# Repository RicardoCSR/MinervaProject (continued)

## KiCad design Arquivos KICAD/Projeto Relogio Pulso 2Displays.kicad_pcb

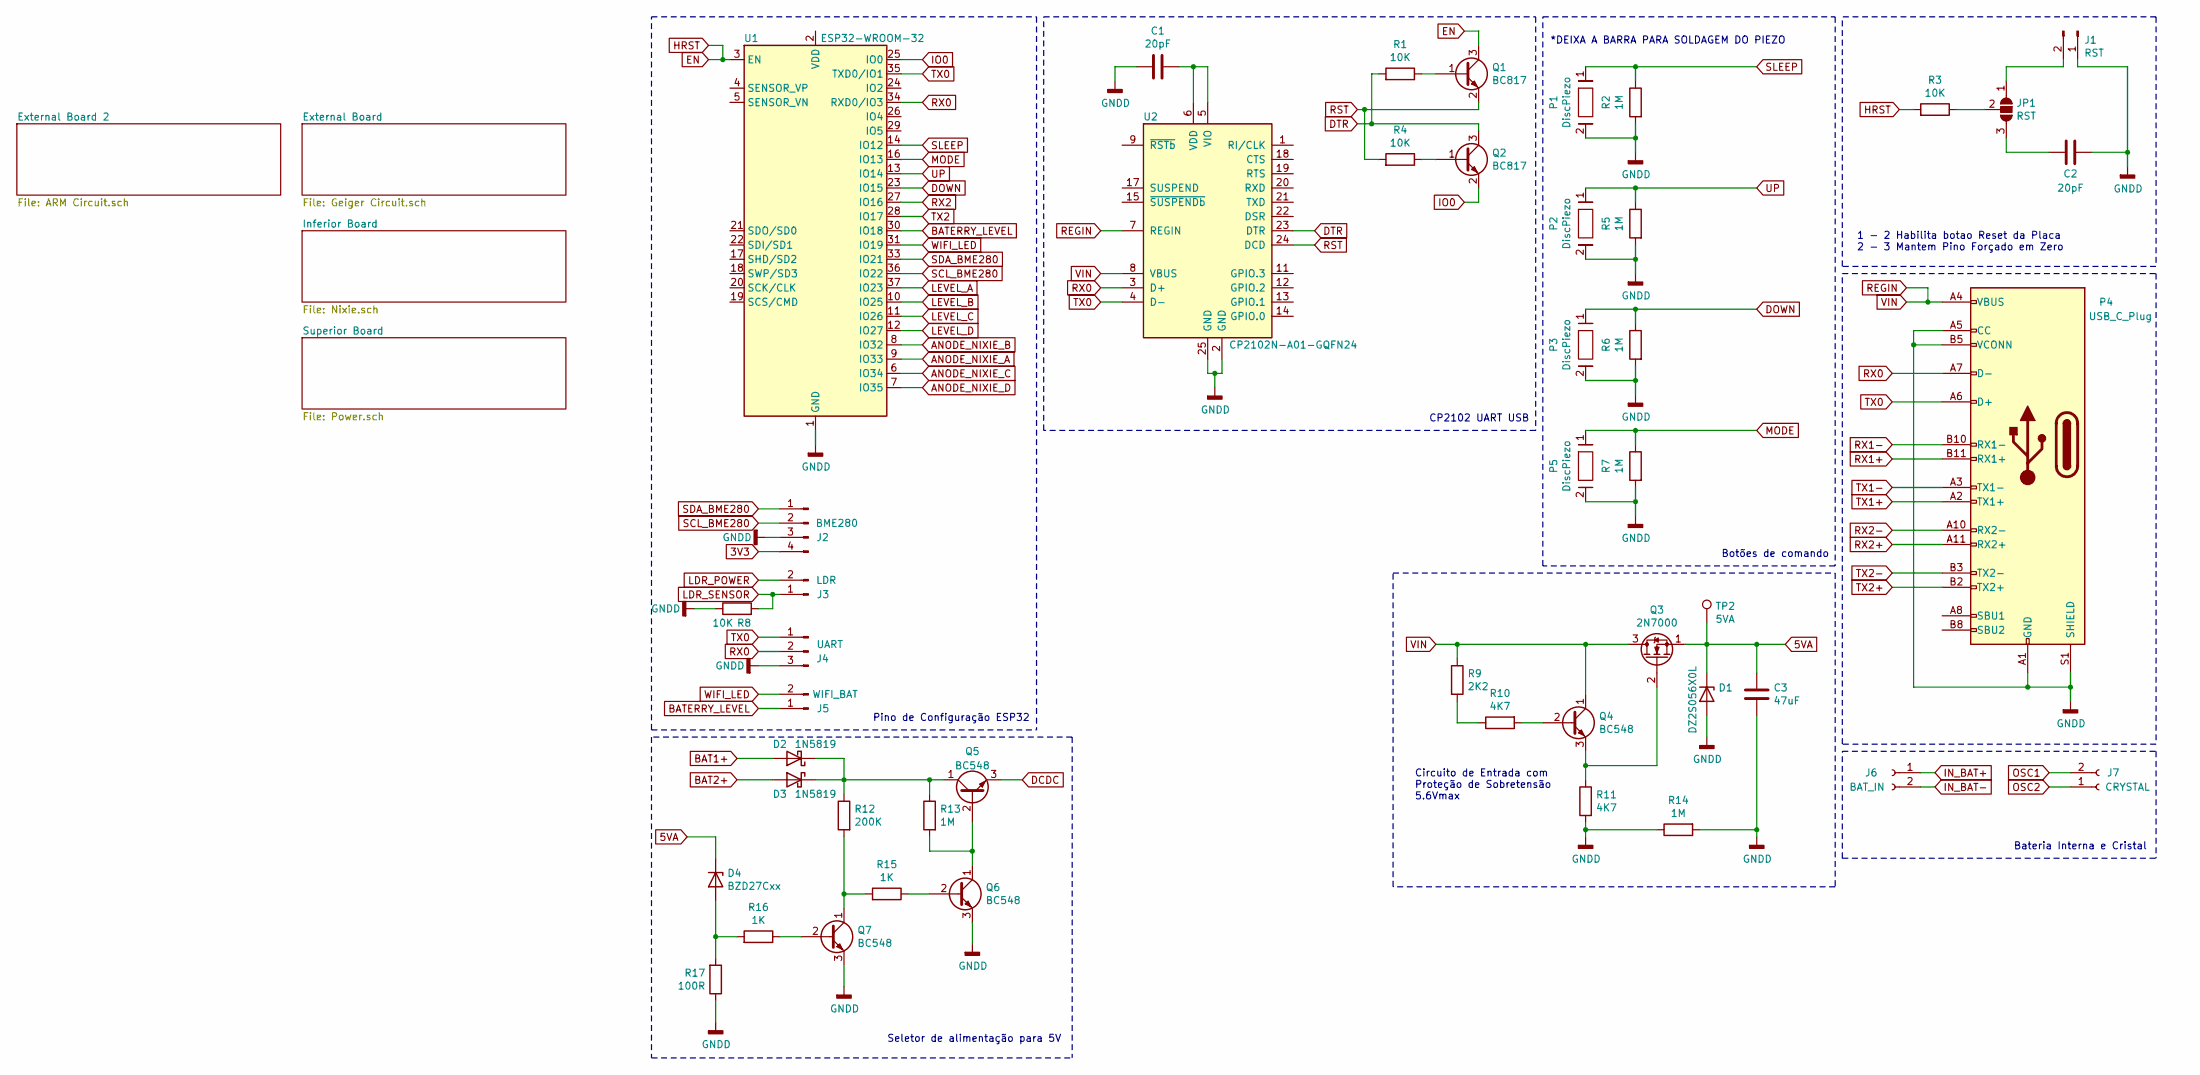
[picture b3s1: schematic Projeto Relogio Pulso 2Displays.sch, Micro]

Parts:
C1, C2: 20pF; C_0805_2012Metric
C3: 47uF; C_0805_2012Metric
D1: DZ2S056X0L; D_2114_3652Metric_Castellated
D2, D3: 1N5819; D_0805_2012Metric
D4: BZD27Cxx; D_2114_3652Metric_Castellated
J1: RST; PinHeader_1x02_P2.00mm_Vertical
J2: BME280; PinHeader_2x02_P2.00mm_Vertical
J3: LDR; PinHeader_1x02_P2.00mm_Vertical
J4: UART; PinHeader_1x03_P2.00mm_Vertical
J5: WIFI_BAT; PinHeader_1x02_P2.00mm_Vertical
J6: BAT_IN; PinHeader_1x02_P2.00mm_Vertical
J7: CRYSTAL; PinHeader_1x02_P2.00mm_Vertical
JP1: RST; SolderJumper-3_P1.3mm_Open_RoundedPad1.0x1.5mm_NumberLabels
P1, P2, P3, P5: DiscPiezo; PinHeader_1x02_P1.27mm_Vertical
P4: USB_C_Plug; USB_C_Receptacle_Palconn_UTC16-G
Q1, Q2: BC817; SOT-23
Q3: 2N7000; SOT-23
Q4, Q5, Q6, Q7: BC548; SOT-23
R1, R3, R4, R8: 10K; R_0603_1608Metric
R2, R5, R6, R7, R13, R14: 1M; R_0603_1608Metric
R9: 2K2; R_0603_1608Metric
R10, R11: 4K7; R_0603_1608Metric
R12: 200K; R_0603_1608Metric
R15, R16: 1K; R_0603_1608Metric
R17: 100R; R_0603_1608Metric
TP2: 5VA; TestPoint_Pad_1.5x1.5mm
U1: ESP32-WROOM-32
U2: CP2102N-A01-GQFN24; QFN-24-1EP_4x4mm_P0.5mm_EP2.6x2.6mm

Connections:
3V3: J2.4; also elsewhere on the board
5VA: C3.1, D1.1 (K), D4.1 (K), Q3.1 (S), TP2.1; also elsewhere on the board
ANODE_NIXIE_A: U1.9 (IO33); also elsewhere on the board
ANODE_NIXIE_B: U1.8 (IO32); also elsewhere on the board
ANODE_NIXIE_C: U1.6 (IO34); also elsewhere on the board
ANODE_NIXIE_D: U1.7 (IO35); also elsewhere on the board
BAT1+: D2.2 (A), J6.1; also elsewhere on the board
BAT1-: C1.2, C2.2, C3.2, D1.2 (A), J1.1, J2.3, J4.3, P1.2, P2.2, P3.2, P4.A1 (GND), P4.A5 (CC), P4.A12 (GND), P4.B1 (GND), P4.B5 (VCONN), P4.B12 (GND), P4.S1 (SHIELD), P5.2, Q6.3 (E), Q7.3 (E), R2.2, R5.2, R6.2, R7.2, R8.1, R11.2, R14.1, R14.2, R17.1, U1.1 (GND), U1.15 (GND), U1.38 (GND), U1.39 (GND), U2.2 (GND), U2.25 (GND); also elsewhere on the board
BAT2+: D3.2 (A); also elsewhere on the board
BATERRY_LEVEL: J5.1, U1.30 (IO18); also elsewhere on the board
DCDC: Q5.3 (E); also elsewhere on the board
DOWN: P3.1, R6.1, U1.23 (IO15); also elsewhere on the board
DTR: Q2.3 (C), R1.2, U2.23 (DTR)
EN: Q1.3 (C), R3.2, U1.3 (EN); also elsewhere on the board
IN_BAT-: J6.2; also elsewhere on the board
IO0: Q2.2 (E), U1.25 (IO0)
LDR_POWER: J3.2; also elsewhere on the board
LDR_SENSOR: J3.1, R8.2; also elsewhere on the board
LEVEL_A: U1.37 (IO23); also elsewhere on the board
LEVEL_B: U1.10 (IO25); also elsewhere on the board
LEVEL_C: U1.11 (IO26); also elsewhere on the board
LEVEL_D: U1.12 (IO27); also elsewhere on the board
MODE: P5.1, R7.1, U1.16 (IO13); also elsewhere on the board
unnamed: C1.1, U2.5 (VIO), U2.6 (VDD)
unnamed: C2.1, JP1.3 (B)
unnamed: D2.1 (K), D3.1 (K), Q5.1 (C), R12.1, R13.1
unnamed: D4.2 (A), R16.2, R17.2
unnamed: J1.2, JP1.1 (A)
unnamed: JP1.2 (C), R3.1
unnamed: Q1.1 (B), R1.1
unnamed: Q2.1 (B), R4.1
unnamed: Q3.2 (G), Q4.3 (E), R11.1
unnamed: Q4.2 (B), R10.2
unnamed: Q5.2 (B), Q6.1 (C), R13.2
unnamed: Q6.2 (B), R15.1
unnamed: Q7.1 (C), R12.2, R15.2
unnamed: Q7.2 (B), R16.1
unnamed: R9.2, R10.1
REGIN: P4.A4 (VBUS), P4.A9 (VBUS), P4.B4 (VBUS), P4.B9 (VBUS), Q3.3 (D), Q4.1 (C), R9.1, U2.7 (REGIN), U2.8 (VBUS)
RST: Q1.2 (E), R4.2, U2.24 (DCD)
RX0: J4.2, P4.A7 (D-), U1.34 (RXD0/IO3), U2.3 (D+); also elsewhere on the board
RX2: U1.27 (IO16)
SCL_BME280: J2.2, U1.36 (IO22); also elsewhere on the board
SDA_BME280: J2.1, U1.33 (IO21); also elsewhere on the board
SLEEP: P1.1, R2.1, U1.14 (IO12); also elsewhere on the board
TX0: J4.1, P4.A6 (D+), U1.35 (TXD0/IO1), U2.4 (D-); also elsewhere on the board
TX2: U1.28 (IO17)
UP: P2.1, R5.1, U1.13 (IO14); also elsewhere on the board
WIFI_LED: J5.2, U1.31 (IO19); also elsewhere on the board

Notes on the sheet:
1 - 2 Habilita botao Reset da Placa 2 - 3 Mantem Pino Forçado em Zero
*DEIXA A BARRA PARA SOLDAGEM DO PIEZO
Botões de comando
Seletor de alimentação para 5V
Pino de Configuração ESP32
CP2102 UART USB
Bateria Interna e Cristal
Circuito de Entrada com Proteção de Sobretensão 5.6Vmax

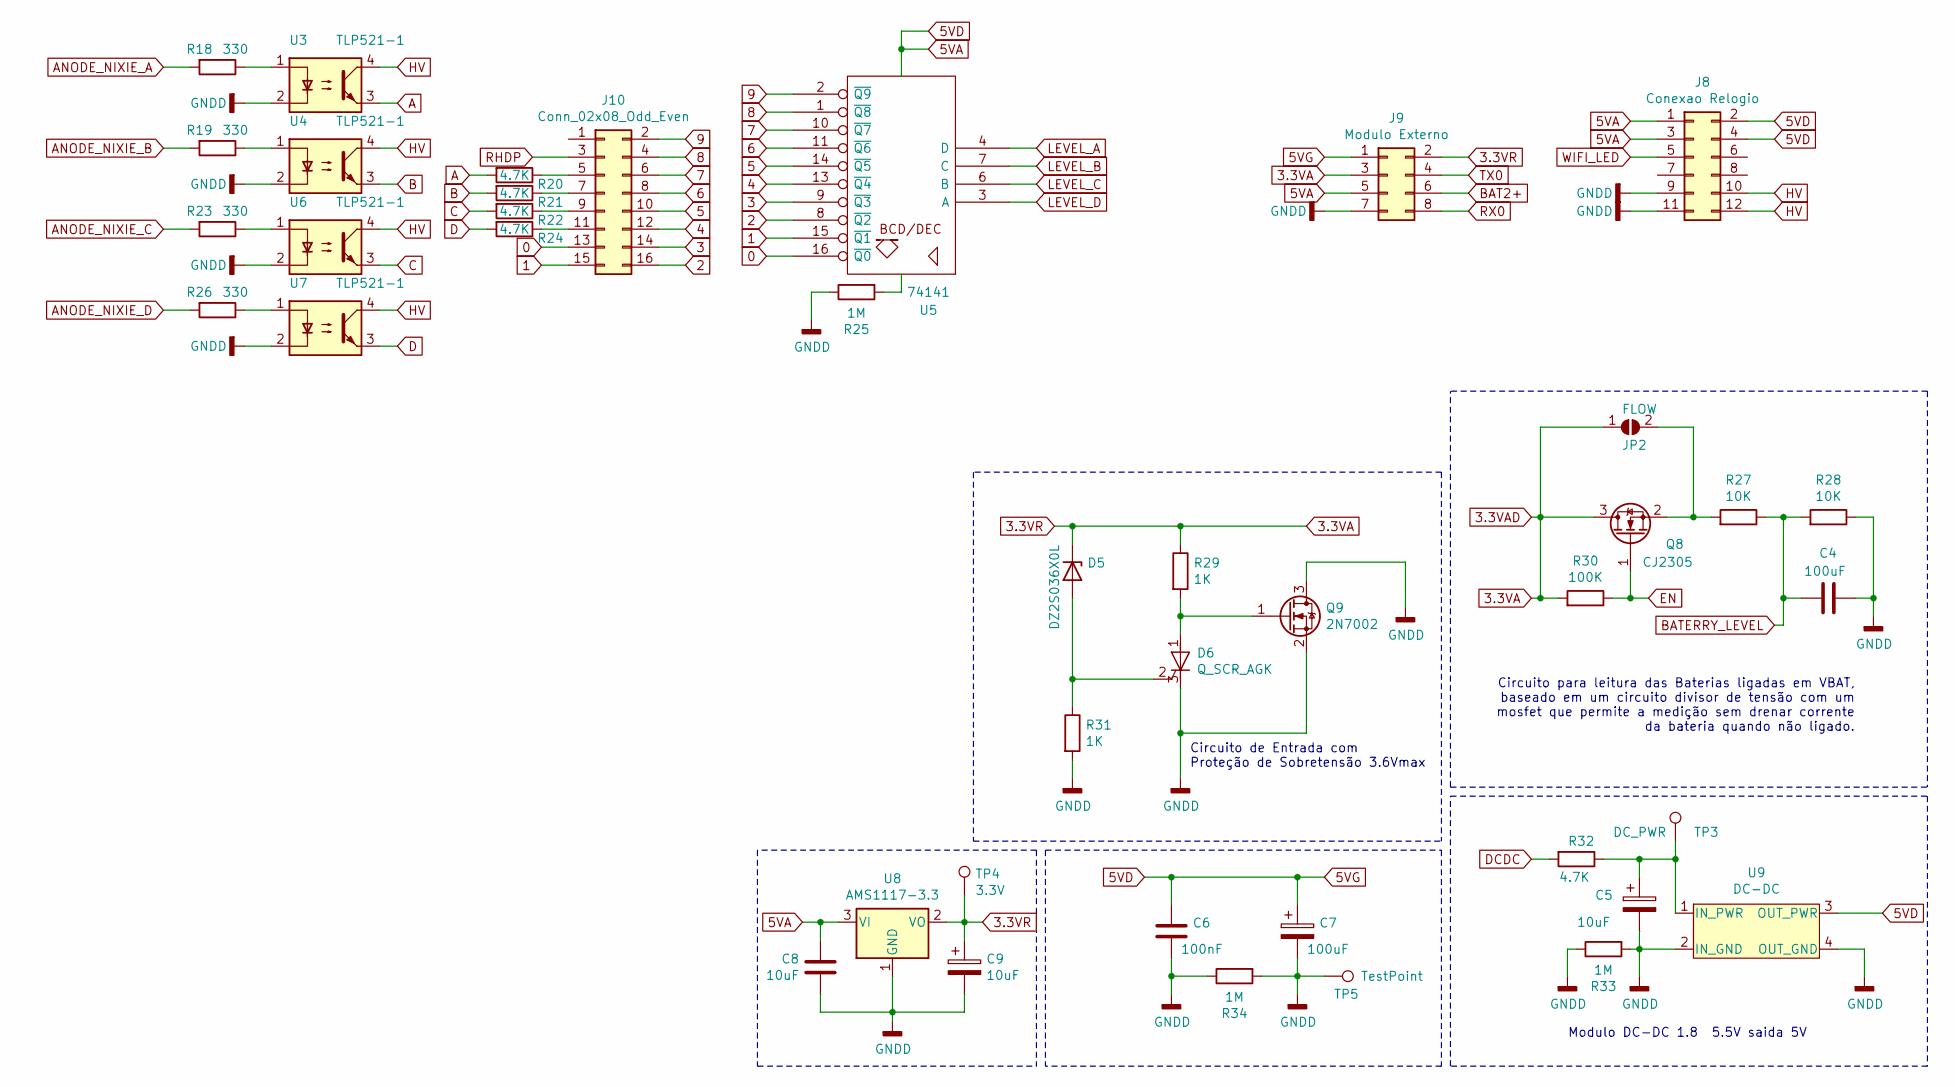
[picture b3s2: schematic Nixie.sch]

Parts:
C4, C7: 100uF; C_0805_2012Metric
C5, C8, C9: 10uF; C_0805_2012Metric
C6: 100nF; C_0805_2012Metric
D5: DZ2S036X0L; D_2114_3652Metric_Castellated
D6: Q_SCR_AGK; SOT-23
J8: Conexao Relogio; PinHeader_2x06_P2.00mm_Vertical
J9: Modulo Externo; Molex_Nano-Fit_105310-xx08_2x04_P2.50mm_Vertical
J10: Conn_02x08_Odd_Even; PinHeader_2x08_P2.00mm_Vertical
JP2: FLOW; SolderJumper-2_P1.3mm_Open_RoundedPad1.0x1.5mm
Q8: CJ2305; SOT-23
Q9: 2N7002; SOT-23
R18, R19, R23, R26: 330; R_0603_1608Metric
R20, R21, R22, R24, R32: 4.7K; R_0603_1608Metric
R25, R33, R34: 1M; R_0603_1608Metric
R27, R28: 10K; R_0603_1608Metric
R29, R31: 1K; R_0603_1608Metric
R30: 100K; R_0603_1608Metric
TP3: DC_PWR; TestPoint_Pad_1.5x1.5mm
TP4: 3.3V; TestPoint_Pad_1.5x1.5mm
TP5: TestPoint; TestPoint_Pad_1.5x1.5mm
U3, U4, U6, U7: TLP521-1; DIP-4_W7.62mm
U5: 74141; DIP-16_W7.62mm
U8: AMS1117-3.3; SOT-223-3_TabPin2
U9: DC-DC; DCDC_2V~5V

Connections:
0: J10.13, U5.16 (~Q0)
1: J10.15, U5.15 (~Q1)
2: J10.16, U5.8 (~Q2)
3: J10.14, U5.9 (~Q3)
3.3VA: C9.1, D5.1 (K), J9.2, J9.3, JP2.1 (A), Q8.3 (D), R29.1, R30.2, TP4.1, U8.2 (VO); also elsewhere on the board
4: J10.12, U5.13 (~Q4)
5: J10.10, U5.14 (~Q5)
5VA: C6.1, C7.1, C8.1, J8.1, J8.2, J8.3, J8.4, J9.1, J9.5, U5.12 (GND), U8.3 (VI), U9.3 (OUT_PWR); also elsewhere on the board
6: J10.8, U5.11 (~Q6)
7: J10.6, U5.10 (~Q7)
8: J10.4, U5.1 (~Q8)
9: J10.2, U5.2 (~Q9)
A: R20.2, U3.3
ANODE_NIXIE_A: R18.2; also elsewhere on the board
ANODE_NIXIE_B: R19.2; also elsewhere on the board
ANODE_NIXIE_C: R23.2; also elsewhere on the board
ANODE_NIXIE_D: R26.2; also elsewhere on the board
B: R21.2, U4.3
BAT1-: C4.2, C5.2, C6.2, C7.2, C8.2, C9.2, D6.3 (K), J8.9, J8.11, J9.7, Q9.2 (S), Q9.3 (D), R25.1, R28.1, R31.2, R33.1, R33.2, R34.1, R34.2, TP5.1, U3.2, U4.2, U6.2, U7.2, U8.1 (GND), U9.2 (IN_GND), U9.4 (OUT_GND); also elsewhere on the board
BAT2+: J9.6; also elsewhere on the board
BATERRY_LEVEL: C4.1, R27.1, R28.2; also elsewhere on the board
C: R22.2, U6.3
D: R24.2, U7.3
DCDC: R32.2; also elsewhere on the board
EN: Q8.1 (G), R30.1; also elsewhere on the board
HV: J8.10, J8.12, U3.4, U4.4, U6.4, U7.4; also elsewhere on the board
LEVEL_A: U5.4 (D); also elsewhere on the board
LEVEL_B: U5.7 (C); also elsewhere on the board
LEVEL_C: U5.6 (B); also elsewhere on the board
LEVEL_D: U5.3 (A); also elsewhere on the board
unnamed: C5.1, R32.1, TP3.1, U9.1 (IN_PWR)
unnamed: D5.2 (A), D6.2 (G), R31.1
unnamed: D6.1 (A), Q9.1 (G), R29.2
unnamed: J10.5, R20.1
unnamed: J10.7, R21.1
unnamed: J10.9, R22.1
unnamed: J10.11, R24.1
unnamed: JP2.2 (B), Q8.2 (S), R27.2
unnamed: R18.1, U3.1
unnamed: R19.1, U4.1
unnamed: R23.1, U6.1
unnamed: R26.1, U7.1
RHDP: J10.3
RX0: J9.8; also elsewhere on the board
TX0: J9.4; also elsewhere on the board
VCC: R25.2, U5.5 (VCC)
WIFI_LED: J8.5; also elsewhere on the board

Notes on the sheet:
Modulo DC-DC 1.8 ~ 5.5V saida 5V
Circuito para leitura das Baterias ligadas em VBAT, baseado em um circuito divisor de tensão com um mosfet que permite a medição sem drenar corrente da bateria quando não ligado.
Circuito de Entrada com Proteção de Sobretensão 3.6Vmax

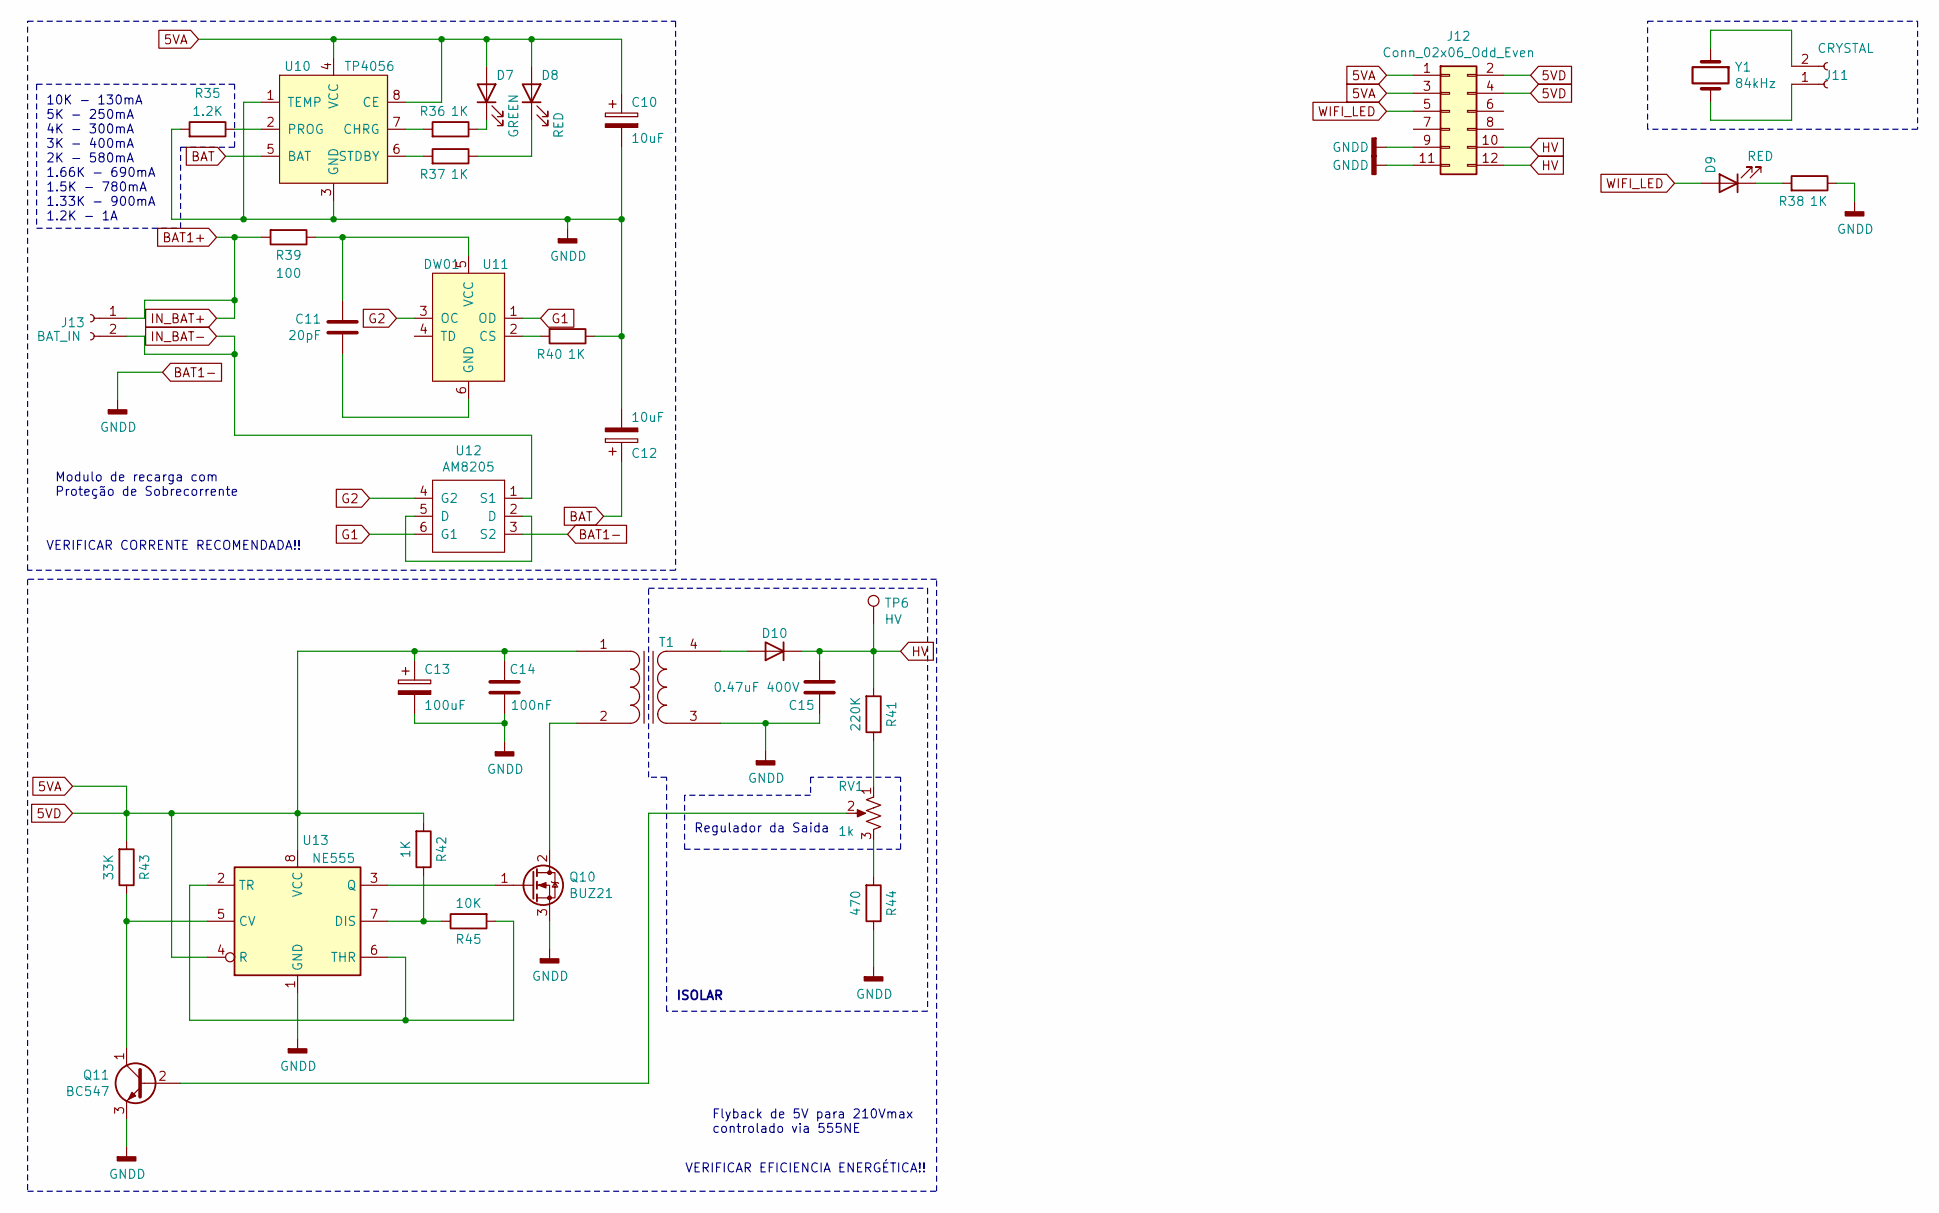
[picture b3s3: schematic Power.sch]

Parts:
C10, C12: 10uF; C_1806_4516Metric
C11: 20pF; C_0805_2012Metric
C13: 100uF; C_1806_4516Metric
C14: 100nF; C_0805_2012Metric
C15: 0.47uF 400V; C_1210_3225Metric
D7: GREEN; LED_1206_3216Metric
D8, D9: RED; LED_1206_3216Metric
D10: DIODE; D_2114_3652Metric_Castellated
J11: CRYSTAL; PinHeader_1x02_P2.00mm_Vertical
J12: Conn_02x06_Odd_Even; PinHeader_2x06_P2.00mm_Vertical
J13: BAT_IN; PinHeader_1x02_P2.00mm_Vertical
Q10: BUZ21; TO-220-3_Vertical
Q11: BC547; SOT-23
R35: 1.2K; R_0603_1608Metric
R36, R37, R38, R40, R42: 1K; R_0603_1608Metric
R39: 100; R_0603_1608Metric
R41: 220K; R_0603_1608Metric
R43: 33K; R_0603_1608Metric
R44: 470; R_0603_1608Metric
R45: 10K; R_0603_1608Metric
RV1: 1k; Potentiometer_Bourns_3339P_Vertical_HandSoldering
T1: Transformer_1P_1S; Transformer_CEEH54_Nixie
TP6: HV; TestPoint_Pad_1.5x1.5mm
U10: TP4056; SOIC-8_5.275x5.275mm_P1.27mm
U11: DW01; TSSOP-8_4.4x3mm_P0.65mm
U12: AM8205; SOT-23-6
U13: NE555; SOIC-8_5.275x5.275mm_P1.27mm
Y1: 84kHz; Crystal_AT310_D3.0mm_L10.0mm_Vertical

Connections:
5VA: C10.1, C13.1, C14.1, D7.2 (A), D8.2 (A), J12.1, J12.2, J12.3, J12.4, R42.2, R43.2, T1.1 (AA), U10.4 (VCC), U10.8 (CE), U13.4 (R), U13.8 (VCC); also elsewhere on the board
BAT: C12.1, U10.5 (BAT); also elsewhere on the board
BAT1+: J13.1, R39.2; also elsewhere on the board
BAT1-: C10.2, C12.2, C13.2, C14.2, C15.2, J12.9, J12.11, Q10.3 (S), Q11.3 (E), R35.2, R38.1, R40.1, R44.1, T1.3 (SA), U10.1 (TEMP), U10.3 (GND), U12.3 (S2), U13.1 (GND); also elsewhere on the board
G1: U11.1 (OD), U12.6 (G1); also elsewhere on the board
G2: U11.3 (OC), U12.4 (G2); also elsewhere on the board
HV: C15.1, D10.2 (K), J12.10, J12.12, R41.2, TP6.1; also elsewhere on the board
IN_BAT-: J13.2, U12.1 (S1); also elsewhere on the board
unnamed: C11.1, U11.6 (GND)
unnamed: C11.2, R39.1, U11.5 (VCC)
unnamed: D7.1 (K), R36.1
unnamed: D8.1 (K), R37.1
unnamed: D9.1 (K), R38.2
unnamed: D10.1 (A), T1.4 (SB)
unnamed: J11.1, Y1.2
unnamed: J11.2, Y1.1
unnamed: Q10.1 (G), U13.3 (Q)
unnamed: Q10.2 (D), T1.2 (AB)
unnamed: Q11.1 (C), R43.1, U13.5 (CV)
unnamed: Q11.2 (B), RV1.2
unnamed: R35.1, U10.2 (PROG)
unnamed: R36.2, U10.7 (CHRG)
unnamed: R37.2, U10.6 (STDBY)
unnamed: R40.2, U11.2 (CS)
unnamed: R41.1, RV1.1
unnamed: R42.1, R45.1, U13.7 (DIS)
unnamed: R44.2, RV1.3
unnamed: R45.2, U13.2 (TR), U13.6 (THR)
unnamed: U12.2 (D), U12.5 (D)
WIFI_LED: D9.2 (A), J12.5; also elsewhere on the board

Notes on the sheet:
10K - 130mA 5K - 250mA 4K - 300mA 3K - 400mA 2K - 580mA 1.66K - 690mA 1.5K - 780mA 1.33K - 900mA 1.2K - 1A
Modulo de recarga com Proteção de Sobrecorrente
VERIFICAR CORRENTE RECOMENDADA!!
Flyback de 5V para 210Vmax controlado via 555NE
VERIFICAR EFICIENCIA ENERGÉTICA!!
Regulador da Saida
ISOLAR

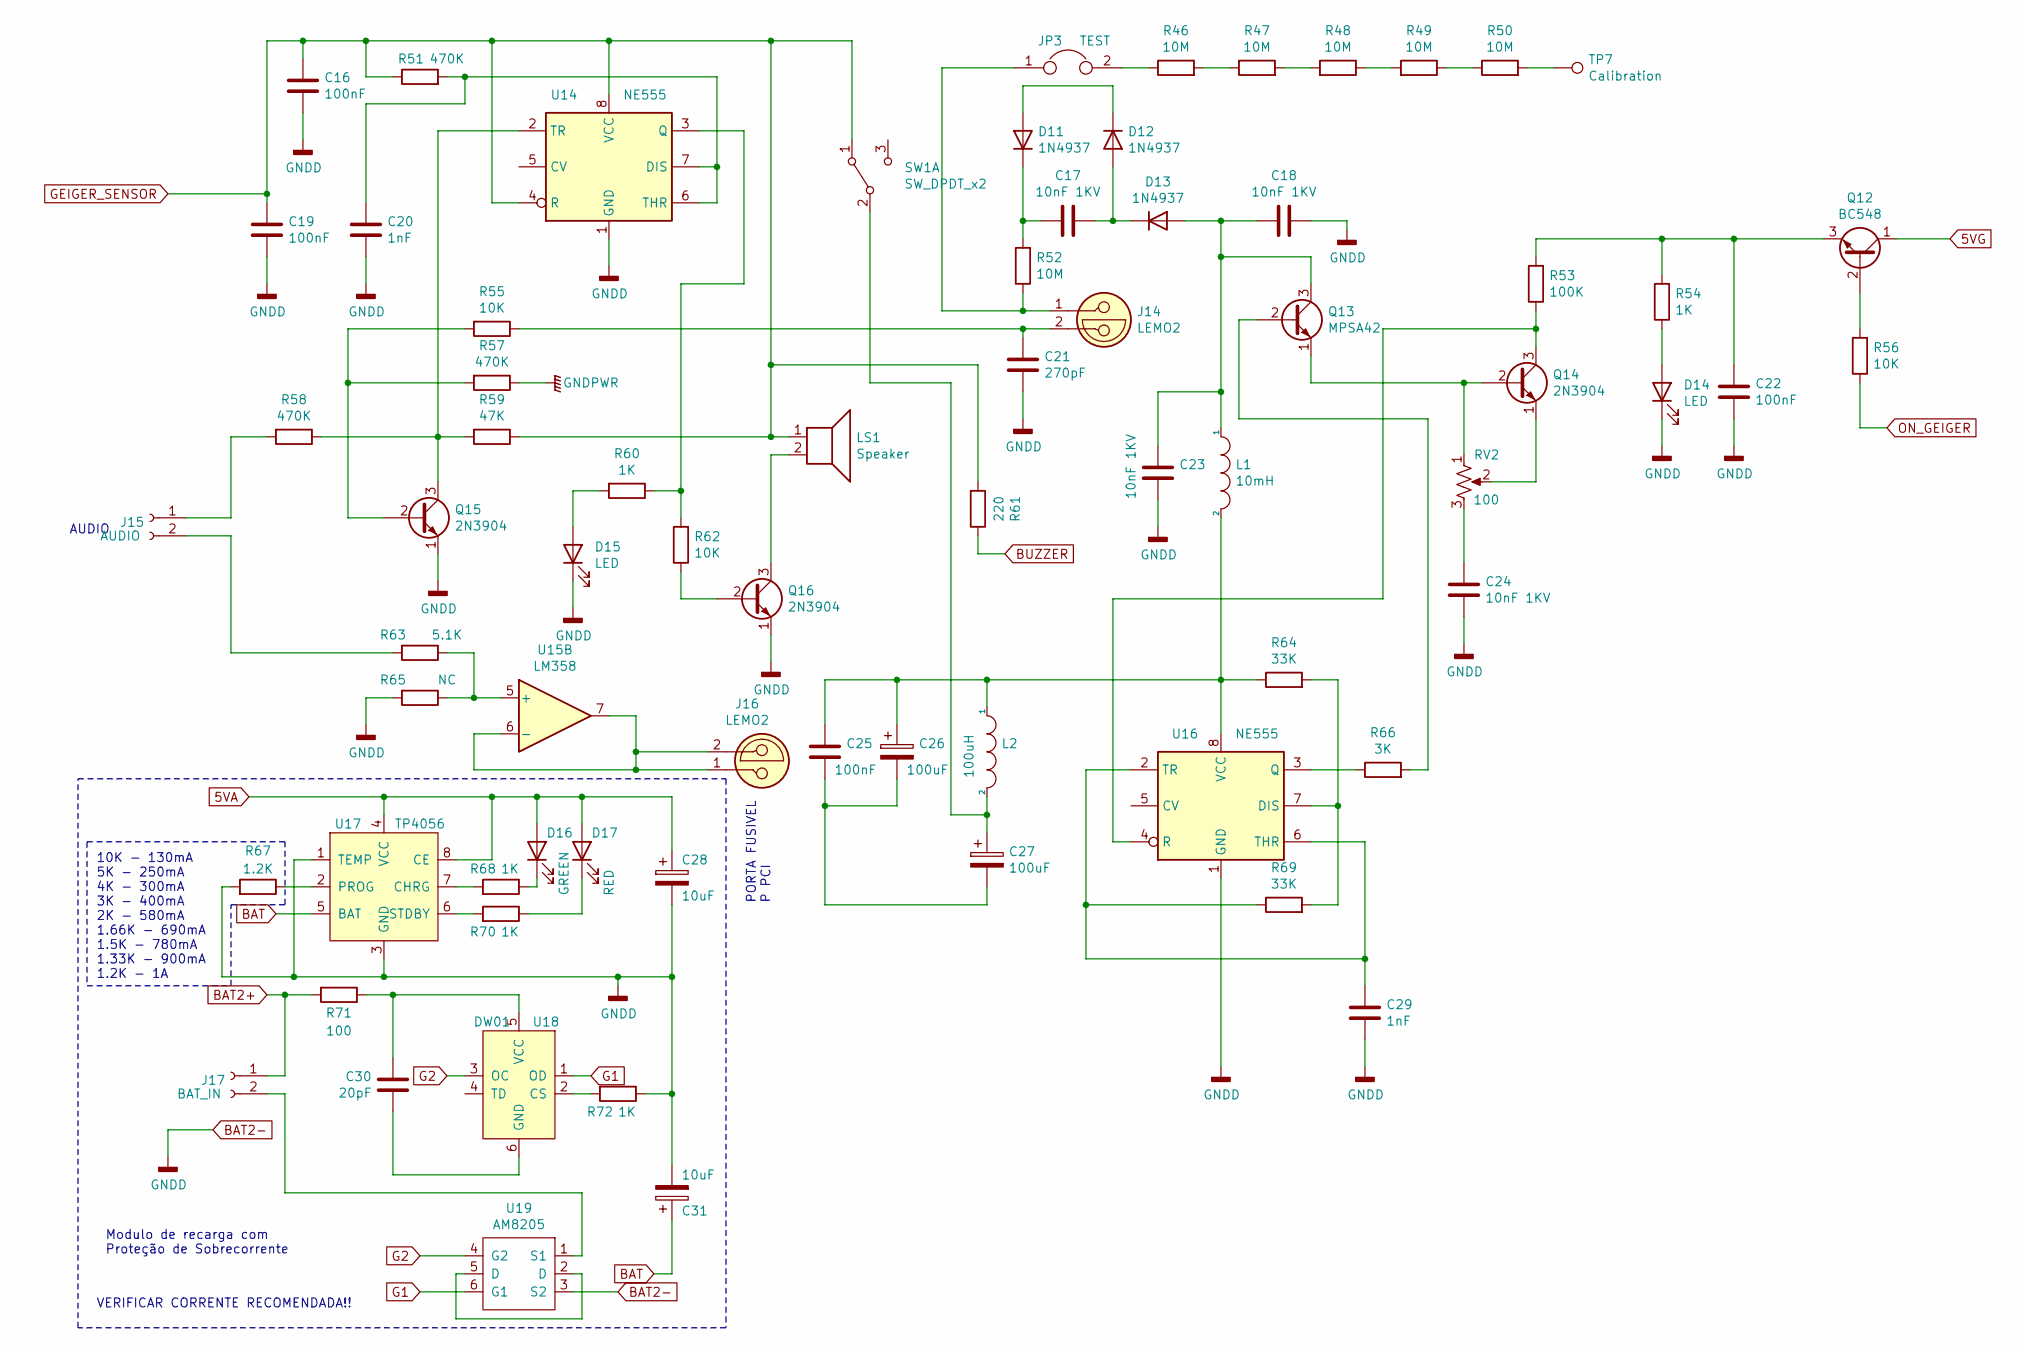
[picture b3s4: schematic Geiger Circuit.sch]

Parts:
C16, C19, C22, C25: 100nF; C_0805_2012Metric
C17, C18, C23, C24: 10nF 1KV; C_1806_4516Metric
C20, C29: 1nF; C_0805_2012Metric
C21: 270pF; C_0805_2012Metric
C26, C27: 100uF; CP_Elec_5x4.5
C28, C31: 10uF; C_1806_4516Metric
C30: 20pF; C_0805_2012Metric
D11, D12, D13: 1N4937; D_2114_3652Metric_Castellated
D14, D15: LED; LED_1206_3216Metric
D16: GREEN; LED_1206_3216Metric
D17: RED; LED_1206_3216Metric
J14, J16: LEMO2; PinHeader_1x02_P2.54mm_Vertical
J15: AUDIO; PinHeader_1x02_P2.00mm_Vertical
J17: BAT_IN; PinHeader_1x02_P2.00mm_Vertical
JP3: TEST; SolderJumper-2_P1.3mm_Open_RoundedPad1.0x1.5mm
L1: 10mH; L_Radial_D7.2mm_P3.00mm_MuRATA_1700
L2: 100uH; L_Radial_D7.2mm_P3.00mm_MuRATA_1700
LS1: Speaker; MagneticBuzzer_Kingstate_KCG0601
Q12: BC548; SOT-23
Q13: MPSA42; SOT-23
Q14, Q15, Q16: 2N3904; SOT-23
R46, R47, R48, R49, R50, R52: 10M; R_0603_1608Metric
R51, R57, R58: 470K; R_0603_1608Metric
R53: 100K; R_0603_1608Metric
R54, R60, R68, R70, R72: 1K; R_0603_1608Metric
R55, R56, R62: 10K; R_0603_1608Metric
R59: 47K; R_0603_1608Metric
R61: 220; R_0603_1608Metric
R63: 5.1K; R_0603_1608Metric
R64, R69: 33K; R_0603_1608Metric
R65: NC; R_0603_1608Metric
R66: 3K; R_0603_1608Metric
R67: 1.2K; R_0603_1608Metric
R71: 100; R_0603_1608Metric
RV2: 100; Potentiometer_Bourns_3339P_Vertical_HandSoldering
SW1: SW_DPDT_x2; SW_CuK_OS102011MA1QN1_SPDT_Angled
TP7: Calibration; TestPoint_Pad_1.5x1.5mm
U14, U16: NE555; SOIC-8_5.275x5.275mm_P1.27mm
U15: LM358; SOIC-8_5.275x5.275mm_P1.27mm
U17: TP4056; SOIC-8_5.275x5.275mm_P1.27mm
U18: DW01; TSSOP-8_4.4x3mm_P0.65mm
U19: AM8205; SOT-23-6

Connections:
5VA: C28.1, D16.2 (A), D17.2 (A), Q12.1 (C), U17.4 (VCC), U17.8 (CE); also elsewhere on the board
BAT: C31.1, U17.5 (BAT); also elsewhere on the board
BAT1-: C16.2, C18.1, C19.2, C20.2, C21.2, C22.2, C23.1, C24.2, C28.2, C29.2, C31.2, D14.1 (K), D15.1 (K), Q15.1 (E), Q16.1 (E), R65.2, R67.2, R72.1, U14.1 (GND), U16.1 (GND), U17.1 (TEMP), U17.3 (GND), U19.3 (S2); also elsewhere on the board
BAT2+: J17.1, R71.2; also elsewhere on the board
BUZZER: R61.1; also elsewhere on the board
G1: U18.1 (OD), U19.6 (G1); also elsewhere on the board
G2: U18.3 (OC), U19.4 (G2); also elsewhere on the board
GEIGER_SENSOR: C16.1, C19.1, LS1.1, R51.1, R59.1, R61.2, SW1.1 (A), U14.4 (R), U14.8 (VCC); also elsewhere on the board
GNDPWR: R57.1
unnamed: C17.1, D12.1 (A), D13.2 (K)
unnamed: C17.2, D11.2 (K), R52.2
unnamed: C18.2, C23.2, D13.1 (A), L1.1, Q13.3 (C)
unnamed: C20.1, R51.2, U14.6 (THR), U14.7 (DIS)
unnamed: C21.1, J14.2, R55.1
unnamed: C22.1, Q12.3 (E), R53.2, R54.2
unnamed: C24.1, RV2.3
unnamed: C25.1, C26.1, L1.2, L2.1, R64.1, U16.8 (VCC)
unnamed: C25.2, C26.2, C27.2
unnamed: C27.1, L2.2, SW1.2 (B)
unnamed: C29.1, R69.1, U16.2 (TR), U16.6 (THR)
unnamed: C30.1, U18.6 (GND)
unnamed: C30.2, R71.1, U18.5 (VCC)
unnamed: D11.1 (A), D12.2 (K)
unnamed: D14.2 (A), R54.1
unnamed: D15.2 (A), R60.2
unnamed: D16.1 (K), R68.1
unnamed: D17.1 (K), R70.1
unnamed: J14.1, JP3.1, R52.1
unnamed: J15.1, R58.2
unnamed: J15.2, R63.2
unnamed: J16.1, J16.2, U15.6 (-), U15.7
unnamed: J17.2, U19.1 (S1)
unnamed: JP3.2, R46.1
unnamed: LS1.2, Q16.3 (C)
unnamed: Q12.2 (B), R56.2
unnamed: Q13.1 (E), Q14.2 (B), RV2.1
unnamed: Q13.2 (B), R66.2
unnamed: Q14.1 (E), RV2.2
unnamed: Q14.3 (C), R53.1, U16.4 (R)
unnamed: Q15.2 (B), R55.2, R57.2
unnamed: Q15.3 (C), R58.1, R59.2, U14.2 (TR)
unnamed: Q16.2 (B), R62.1
unnamed: R46.2, R47.1
unnamed: R47.2, R48.2
unnamed: R48.1, R49.2
unnamed: R49.1, R50.1
unnamed: R50.2, TP7.1
unnamed: R60.1, R62.2, U14.3 (Q)
unnamed: R63.1, R65.1, U15.5 (+)
unnamed: R64.2, R69.2, U16.7 (DIS)
unnamed: R66.1, U16.3 (Q)
unnamed: R67.1, U17.2 (PROG)
unnamed: R68.2, U17.7 (CHRG)
unnamed: R70.2, U17.6 (STDBY)
unnamed: R72.2, U18.2 (CS)
unnamed: U19.2 (D), U19.5 (D)
ON_GEIGER: R56.1

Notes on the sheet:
AUDIO
10K - 130mA 5K - 250mA 4K - 300mA 3K - 400mA 2K - 580mA 1.66K - 690mA 1.5K - 780mA 1.33K - 900mA 1.2K - 1A
Modulo de recarga com Proteção de Sobrecorrente
VERIFICAR CORRENTE RECOMENDADA!!
PORTA FUSIVEL P PCI

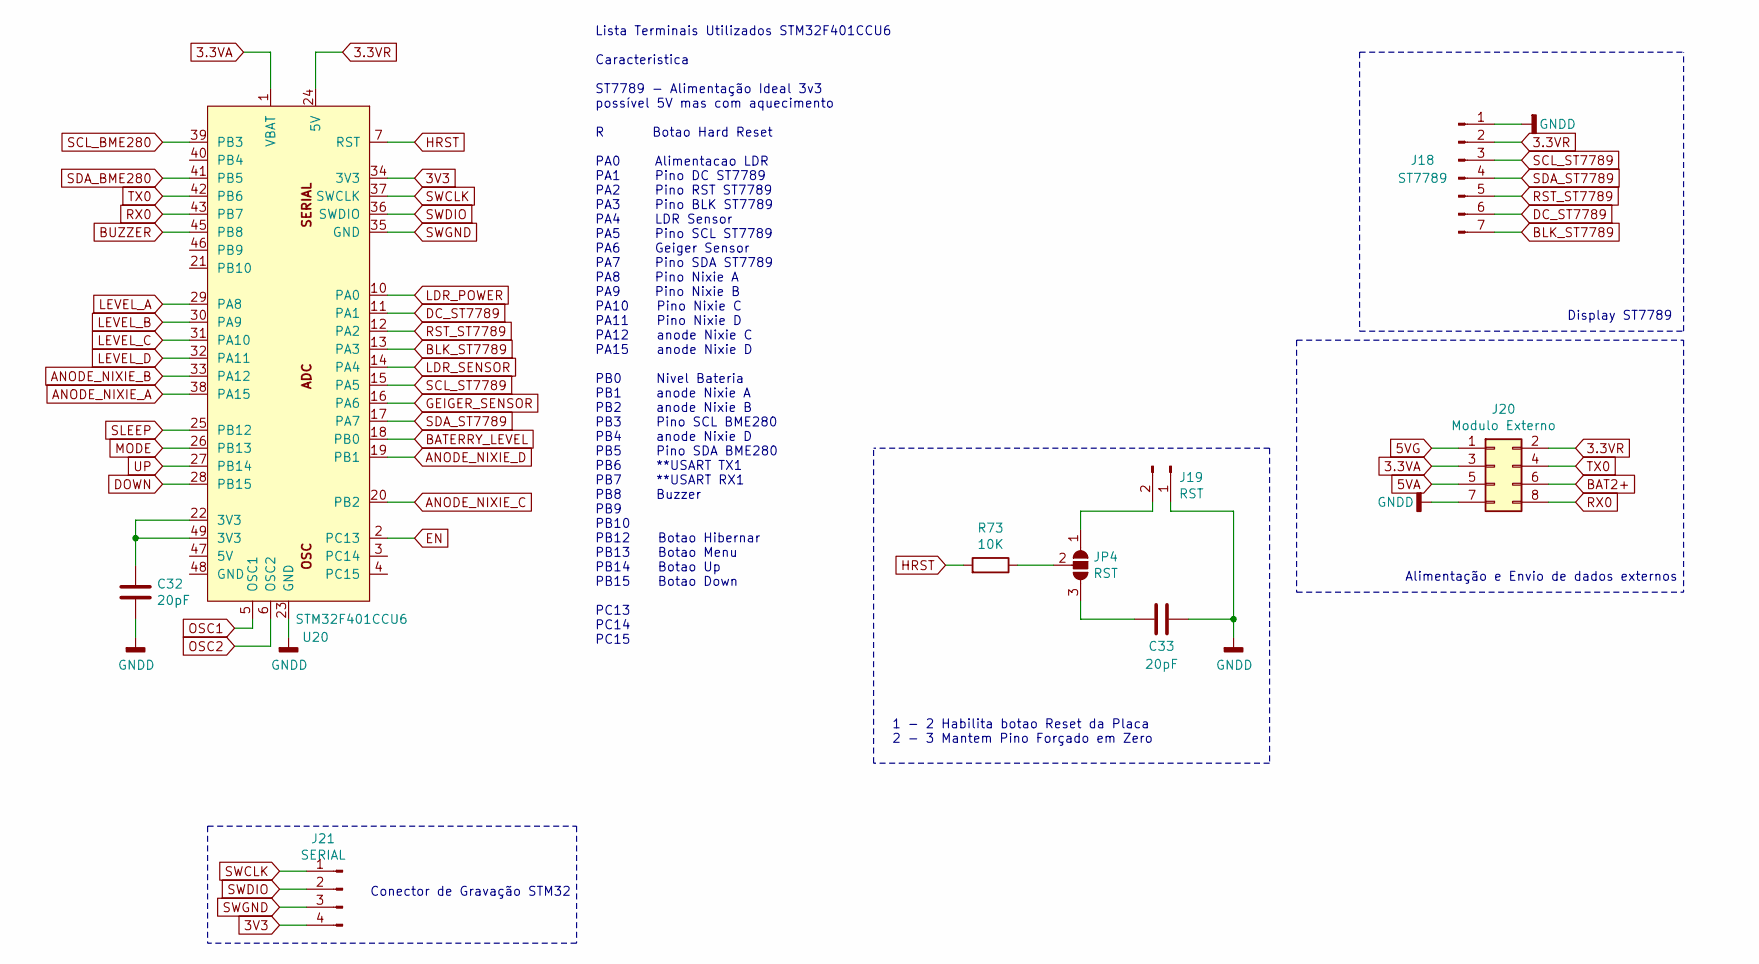
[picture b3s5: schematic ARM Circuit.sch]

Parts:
C32, C33: 20pF; C_0805_2012Metric
J18: ST7789; PinHeader_1x07_P2.54mm_Vertical
J19: RST; PinHeader_1x02_P2.00mm_Vertical
J20: Modulo Externo; Molex_Nano-Fit_105310-xx08_2x04_P2.50mm_Vertical
J21: SERIAL; PinHeader_2x02_P2.00mm_Vertical
JP4: RST; SolderJumper-3_P1.3mm_Open_RoundedPad1.0x1.5mm_NumberLabels
R73: 10K; R_0603_1608Metric
U20: STM32F401CCU6; QFN-48-1EP_7X7mm_P0.5mm_without_thermal

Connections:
3.3VA: J18.2, J20.2, J20.3, U20.1 (VBAT), U20.24 (5V); also elsewhere on the board
3V3: J21.4, U20.34 (3V3); also elsewhere on the board
5VA: J20.1, J20.5; also elsewhere on the board
ANODE_NIXIE_A: U20.38 (PA15); also elsewhere on the board
ANODE_NIXIE_B: U20.33 (PA12); also elsewhere on the board
ANODE_NIXIE_C: U20.20 (PB2); also elsewhere on the board
ANODE_NIXIE_D: U20.19 (PB1); also elsewhere on the board
BAT1-: C32.1, C33.2, J18.1, J19.1, J20.7, U20.23 (GND); also elsewhere on the board
BAT2+: J20.6; also elsewhere on the board
BATERRY_LEVEL: U20.18 (PB0); also elsewhere on the board
BLK_ST7789: J18.7, U20.13 (PA3)
BUZZER: U20.45 (PB8); also elsewhere on the board
DC_ST7789: J18.6, U20.11 (PA1)
DOWN: U20.28 (PB15); also elsewhere on the board
EN: R73.2, U20.2 (PC13), U20.7 (RST); also elsewhere on the board
GEIGER_SENSOR: U20.16 (PA6); also elsewhere on the board
LDR_POWER: U20.10 (PA0); also elsewhere on the board
LDR_SENSOR: U20.14 (PA4); also elsewhere on the board
LEVEL_A: U20.29 (PA8); also elsewhere on the board
LEVEL_B: U20.30 (PA9); also elsewhere on the board
LEVEL_C: U20.31 (PA10); also elsewhere on the board
LEVEL_D: U20.32 (PA11); also elsewhere on the board
MODE: U20.26 (PB13); also elsewhere on the board
unnamed: C32.2, U20.22 (3V3), U20.49 (3V3)
unnamed: C33.1, JP4.3 (B)
unnamed: J19.2, JP4.1 (A)
unnamed: JP4.2 (C), R73.1
OSC1: U20.5 (OSC1)
OSC2: U20.6 (OSC2)
RST_ST7789: J18.5, U20.12 (PA2)
RX0: J20.8, U20.43 (PB7); also elsewhere on the board
SCL_BME280: U20.39 (PB3); also elsewhere on the board
SCL_ST7789: J18.3, U20.15 (PA5)
SDA_BME280: U20.41 (PB5); also elsewhere on the board
SDA_ST7789: J18.4, U20.17 (PA7)
SLEEP: U20.25 (PB12); also elsewhere on the board
SWCLK: J21.1, U20.37 (SWCLK)
SWDIO: J21.2, U20.36 (SWDIO)
SWGND: J21.3, U20.35 (GND)
TX0: J20.4, U20.42 (PB6); also elsewhere on the board
UP: U20.27 (PB14); also elsewhere on the board

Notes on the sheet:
Lista Terminais Utilizados STM32F401CCU6 Caracteristica ST7789 - Alimentação Ideal 3v3 possível 5V mas com aquecimento R Botao Hard Reset PA0 Alimentacao LDR PA1 Pino DC ST7789 PA2 Pino RST ST7789 PA3 Pino BLK ST7789 PA4 LDR Sensor PA5 Pino SCL ST7789 PA6 Geiger Sensor PA7 Pino SDA ST7789 PA8 Pino 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
Conector de Gravação STM32
Display ST7789
Alimentação e Envio de dados externos
1 - 2 Habilita botao Reset da Placa 2 - 3 Mantem Pino Forçado em Zero
